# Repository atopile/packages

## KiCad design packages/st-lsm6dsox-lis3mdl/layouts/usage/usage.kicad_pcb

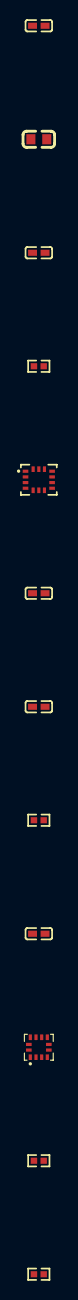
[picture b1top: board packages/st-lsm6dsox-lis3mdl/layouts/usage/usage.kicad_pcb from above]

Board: 2 copper layers, 12 parts (0 on the bottom side), 7 nets, no tracks yet.

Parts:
C1, C2, C3, C5, C6: 100nF ±10% 16V X7R; C0402
C4: 10µF ±20% 6.3V X5R; C0603
R1, R2, R3, R4: 10kΩ ±1% 62.5mW; R0402
U1: LGA-12_L2.0-W2.0-P0.50-BL
U2: LGA-14L_L3.0-W2.5-P0.50-TL

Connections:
C1: C1.1, U1.4
GND: C1.2, C2.2, C3.2, C4.2, C5.2, C6.2, U1.2, U1.3, U1.12, U2.6, U2.7
SCL: R1.2, U1.1, U2.3, U2.13
SDA: R2.2, U1.11, U2.2, U2.14
VCC: C2.1, C3.1, C4.1, C5.1, C6.1, R1.1, R2.1, R3.1, R4.1, U1.5, U1.6, U2.5, U2.8
footprint-CS-0: R3.2, U1.10
footprint-CS-1: R4.2, U2.12

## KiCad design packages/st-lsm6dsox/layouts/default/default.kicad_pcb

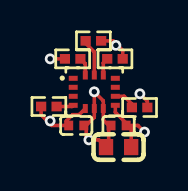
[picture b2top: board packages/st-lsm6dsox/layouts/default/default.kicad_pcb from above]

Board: 2 copper layers, 9 parts (0 on the bottom side), 8 nets.

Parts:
C1: 9.999F; C0603
C2, C3: 1F; C0402
R1, R2, R3, R4, R5: 10000Ω; R0402
U1: LGA-14L_L3.0-W2.5-P0.50-TL

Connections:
4: R4.2, U1.4
9: R5.2, U1.9
CS: R1.2, U1.12
MOSI: R3.2, U1.14
SCL: R2.2, U1.13
hv: C3.1, R1.1, R2.1, R3.1, R4.1, R5.1, U1.5
lv: C1.2, C2.2, C3.2, U1.1, U1.6, U1.7
vdd_cap_10uf-power-hv: C1.1, C2.1, U1.8

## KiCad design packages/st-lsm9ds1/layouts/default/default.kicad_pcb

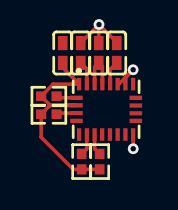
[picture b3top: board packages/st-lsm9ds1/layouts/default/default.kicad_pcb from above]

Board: 2 copper layers, 9 parts (0 on the bottom side), 10 nets.

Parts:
C1, C2, C3, C4: [capacitance: unknown]; C0402
R1, R2, R3, R4: [resistance: unknown]; R0402
U1: LGA-24_L3.5-W3.0-P0.43-TL

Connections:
CS_A_G: R1.2, U1.7
CS_M: R2.2, U1.8
MOSI: R4.2, U1.4
RES: U1.14, U1.15, U1.16, U1.17, U1.18
SCL: R3.2, U1.2
charge_pump_cap-power-hv: C1.1, U1.24
hv: C4.1, R1.1, R2.1, R3.1, R4.1, U1.1, U1.3
ldo_cap-power-hv: C2.1, U1.21
lv: C1.2, C2.2, C3.2, C4.2, U1.5, U1.13, U1.19, U1.20
power_core_cap-power-hv: C3.1, U1.22, U1.23

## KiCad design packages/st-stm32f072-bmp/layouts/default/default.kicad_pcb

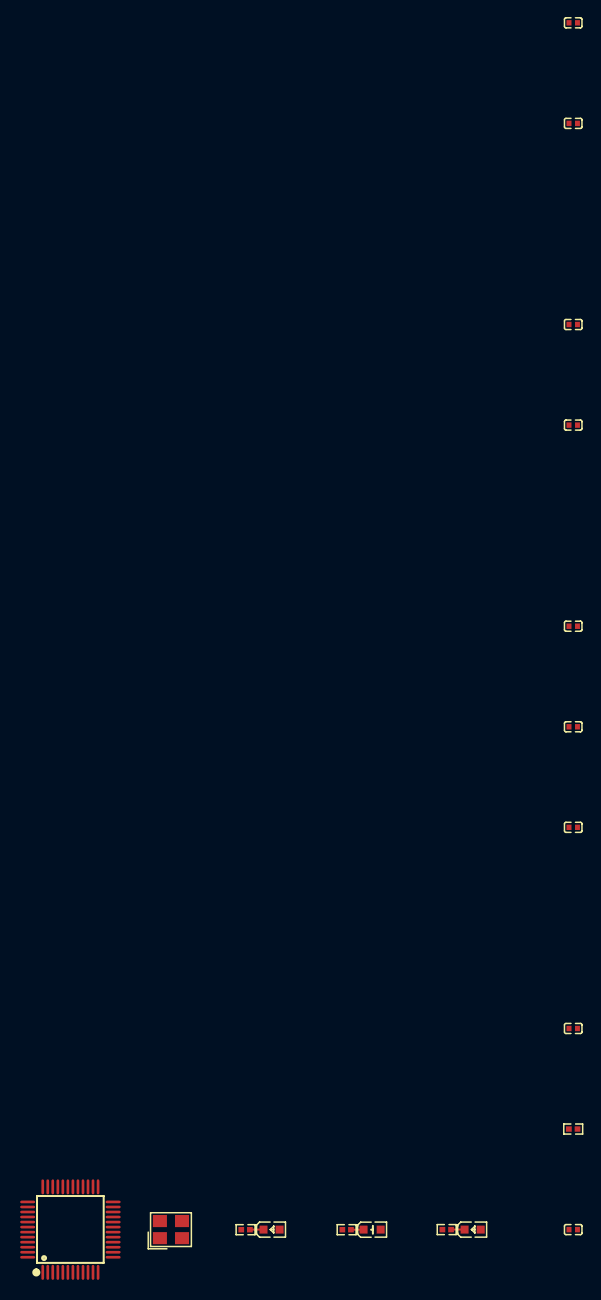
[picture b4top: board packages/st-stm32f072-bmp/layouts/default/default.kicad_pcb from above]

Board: 2 copper layers, 18 parts (0 on the bottom side), 12 nets.

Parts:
C1: 0.000001F; C0402
C2: 0.0000047F; C0402
C3, C4, C5, C6, C9: 0.0000001F; C0402
C7, C8: 0.00000000002F; C0402
LED1, LED2: LED0603-RD
LED3: LED0603-R-RD
R1: 10000Ω; R0402
R2: 0Ω; R0402
R3, R4: 1000Ω; R0402
U1: LQFP-48_L7.0-W7.0-P0.50-LS9.0-BL
X1: CRYSTAL-SMD_4P-L3.2-W2.5-BL

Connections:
44: R1.1, U1.44
XIN: C7.1, U1.5, X1.1
XOUT: C8.1, U1.6, X1.3
anode: C1.1, C2.1, C3.1, C4.1, C5.1, C6.1, LED1.2, LED2.2, LED3.1, U1.1, U1.9, U1.24, U1.36, U1.48
cathode: LED1.1, R2.1
hv: C9.1, U1.7
led_green-power-lv: R2.2, U1.41
led_red-cathode: LED2.1, R3.1
led_red-power-lv: R3.2, U1.43
led_yellow-cathode: LED3.2, R4.1
led_yellow-power-lv: R4.2, U1.42
lv: C1.2, C2.2, C3.2, C4.2, C5.2, C6.2, C7.2, C8.2, C9.2, R1.2, U1.8, U1.23, U1.35, U1.47, X1.2, X1.4

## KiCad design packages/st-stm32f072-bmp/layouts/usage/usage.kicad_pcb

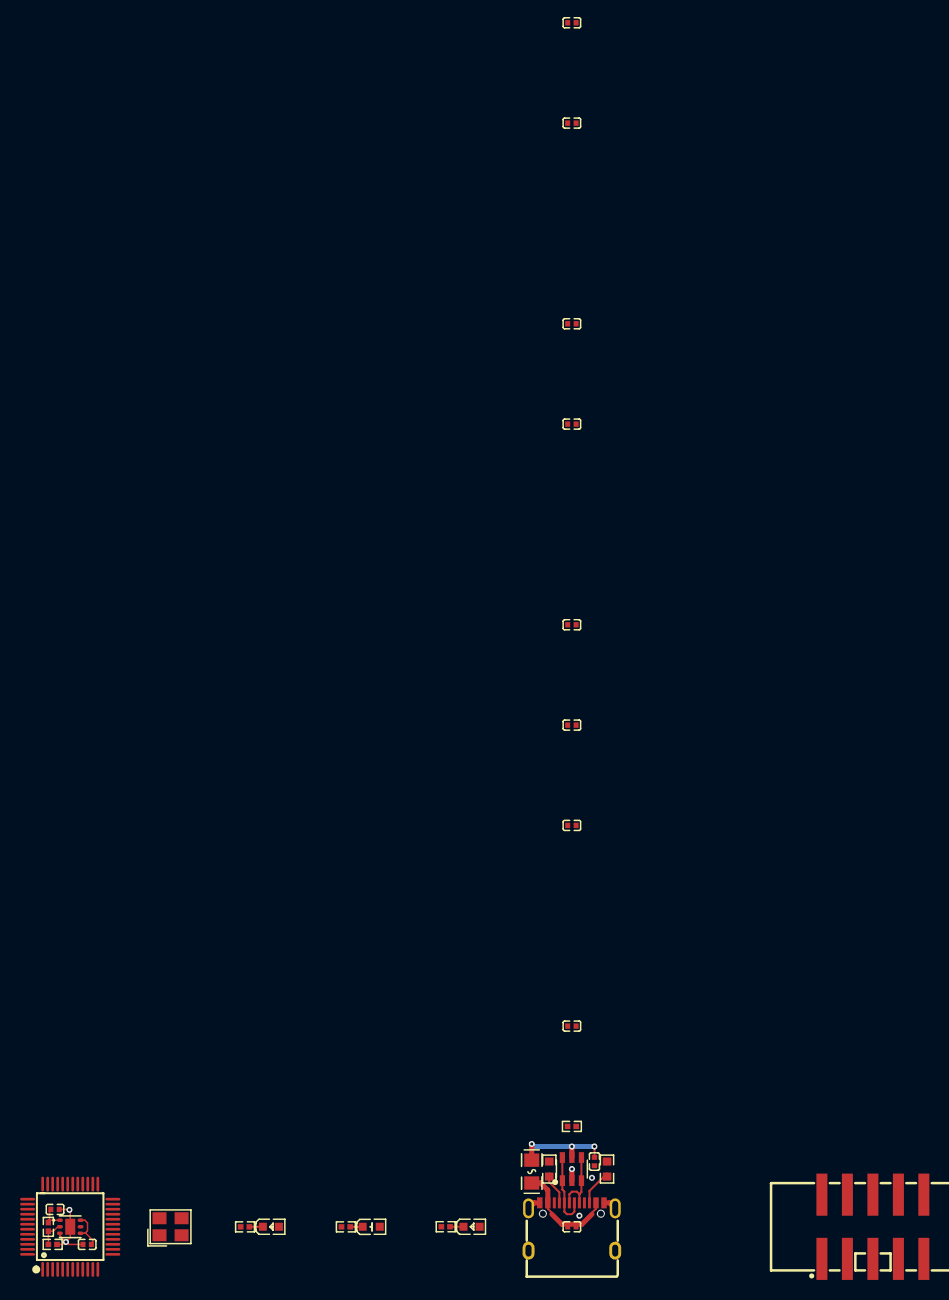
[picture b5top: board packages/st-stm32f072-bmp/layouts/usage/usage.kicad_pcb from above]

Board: 2 copper layers, 30 parts (0 on the bottom side), 25 nets.

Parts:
C1, C11, C12: 0.000001F; C0402
C2: 0.0000047F; C0402
C3, C4, C5, C6, C9, C10: 0.0000001F; C0402
C7, C8: 0.00000000002F; C0402
CN1: IDC-SMD_10P-P2.54-V-R2-C5-S9.50
D4: SOT-23-6_L2.9-W1.6-P0.95-LS2.8-BL
F1: F0805
LED1, LED2: LED0603-RD
LED3: LED0603-R-RD
R1, R7, R8: 10000Ω; R0402
R2: 0Ω; R0402
R3, R4: 1000Ω; R0402
R5, R6: 10000Ω; R0603
U1: LQFP-48_L7.0-W7.0-P0.50-LS9.0-BL
U2: WSON-6_L2.0-W2.0-P0.65-TL-EP
USB1: USB-C-SMD_TYPE-C-6PIN-2MD-073
X1: CRYSTAL-SMD_4P-L3.2-W2.5-BL

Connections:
4: R5.1, USB1.4
10: R6.1, USB1.10
44: R1.1, U1.44
CLK: CN1.4, U1.17
DATA_N: D4.1, D4.6, U1.32, USB1.5, USB1.7
DATA_P: D4.3, D4.4, U1.33, USB1.6, USB1.8
DIO: CN1.2, U1.11
N_RESET: CN1.10, U1.15
SWO: CN1.6, U1.16
TDI: CN1.8, U1.10
XIN: C7.1, U1.5, X1.1
XOUT: C8.1, U1.6, X1.3
anode: C1.1, C2.1, C3.1, C4.1, C5.1, C6.1, C12.1, CN1.1, LED1.2, LED2.2, LED3.1, R7.1, U1.1, U1.9, U1.24, U1.36, U1.48, U2.1
bmp.led_red-cathode: LED2.1, R3.1
bmp.led_yellow-cathode: LED3.2, R4.1
cathode: LED1.1, R2.1
hv: C9.1, U1.7
led_green-power-lv: R2.2, U1.41
led_red-power-lv: R3.2, U1.43
led_yellow-power-lv: R4.2, U1.42
lv: C1.2, C2.2, C3.2, C4.2, C5.2, C6.2, C7.2, C8.2, C9.2, C12.2, CN1.3, CN1.5, CN1.9, R1.2, R8.2, U1.8, U1.23, U1.35, U1.47, U2.7, X1.2, X1.4
power_in-hv: C10.1, C11.1, D4.5, F1.2, U2.4, U2.6
power_vbus-hv: F1.1, USB1.2, USB1.11
ref_out-hv: R7.2, R8.1, U2.2
reference-lv: C10.2, C11.2, D4.2, R5.2, R6.2, U2.3, USB1.1, USB1.12, USB1.13, USB1.14, USB1.15, USB1.16

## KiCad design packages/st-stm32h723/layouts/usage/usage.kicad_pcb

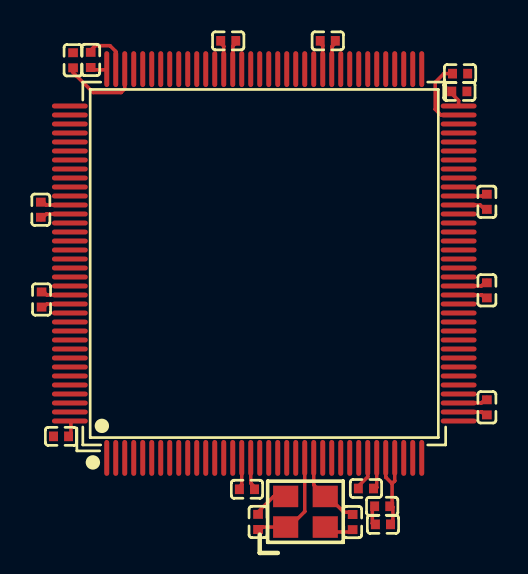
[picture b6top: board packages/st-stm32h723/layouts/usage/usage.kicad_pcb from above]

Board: 2 copper layers, 20 parts (0 on the bottom side), 5 nets.

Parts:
C1, C2, C3, C4, C5, C6, C7, C8, C22, C23, C24, C25, C27: 100nF ±10%; C0402
C9, C10: 18pF ±5%; C0402
C11, C12: 2.2µF ±20%; C0402
C26: 1µF ±10%; C0402
U1: LQFP-144_L20.0-W20.0-P0.50-LS22.0-BL
X1: OSC-SMD_4P-L3.2-W2.5-BL_SIT8008BI

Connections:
XIN: C9.1, U1.23, X1.1
XOUT: C10.1, U1.24, X1.3
hv: C1.1, C2.1, C3.1, C4.1, C5.1, C6.1, C7.1, C8.1, C22.1, C23.1, C24.1, C25.1, C26.1, C27.1, U1.17, U1.30, U1.32, U1.33, U1.39, U1.52, U1.62, U1.72, U1.84, U1.95, U1.108, U1.121, U1.131, U1.144
lv: C1.2, C2.2, C3.2, C4.2, C5.2, C6.2, C7.2, C8.2, C9.2, C10.2, C11.2, C12.2, C22.2, C23.2, C24.2, C25.2, C26.2, C27.2, U1.16, U1.31, U1.38, U1.51, U1.61, U1.83, U1.94, U1.107, U1.120, U1.130, X1.2, X1.4
vcap_caps[1]-power-hv: C11.1, C12.1, U1.71, U1.106
